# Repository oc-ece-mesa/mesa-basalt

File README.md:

# MESA Basalt

<div>

</div>

Basalt is a cost effective and easy to assemble (mostly through-hole components) devboard based on the STM32C071 microcontroller.

## Docs

1. [Parts List](docs/parts-list.md)
2. [Assembly & Setup](docs/assembly-and-setup.md)
3. [Dev Env Setup](docs/dev-env-setup.md)

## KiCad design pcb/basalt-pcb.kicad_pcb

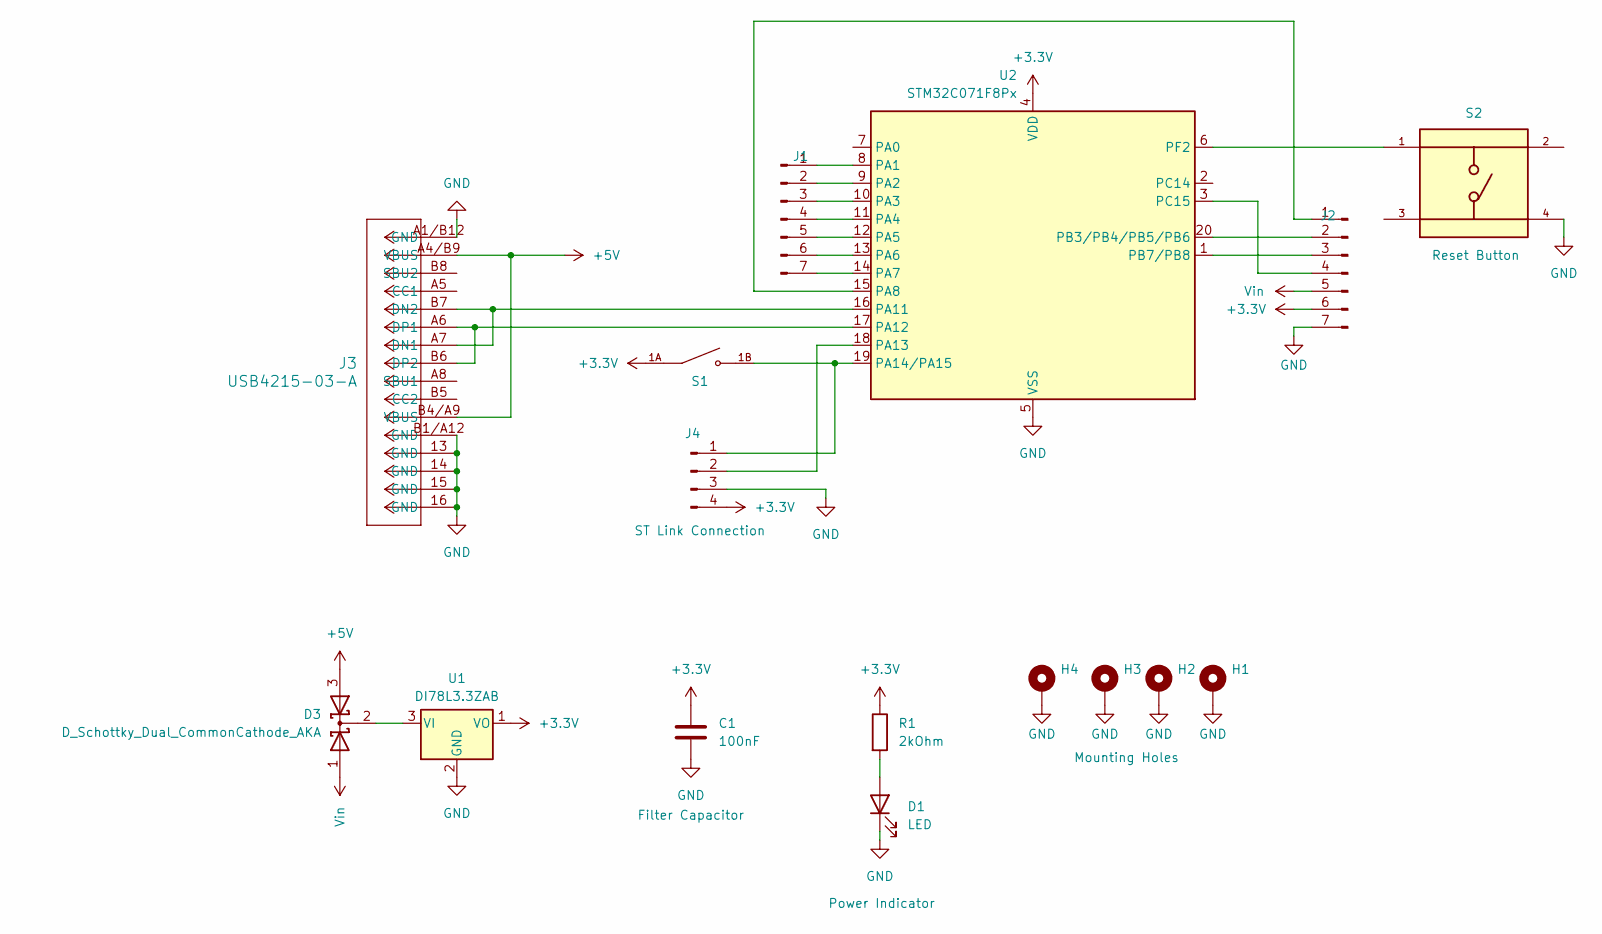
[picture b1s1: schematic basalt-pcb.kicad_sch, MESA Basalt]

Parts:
C1: 100nF; C_Disc_D5.1mm_W3.2mm_P5.00mm
D1: LED; LED_D3.0mm
D3: D_Schottky_Dual_CommonCathode_AKA; TO-220-3_Vertical
H1, H2, H3, H4: MountingHole_Pad; MountingHole_2.2mm_M2_Pad
J1, J2: Conn_01x07_Pin; PinHeader_1x07_P2.54mm_Vertical
J3: USB4215-03-A; CONN_8p94X6p5X3p16_12L_GCC
J4: Conn_01x04_Pin; PinHeader_1x04_P2.54mm_Vertical
R1: 2kOhm; R_Axial_DIN0309_L9.0mm_D3.2mm_P12.70mm_Horizontal
S1: DS04-254-1L-01BK; SW_DS04-254-1L-01BK; PARTREV V0.0
S2: TS02-66-50-BK-260-SCR-D; SW_TS02-66-50-BK-260-SCR-D; PARTREV 1.0
U1: DI78L3.3ZAB; TO-92_Inline
U2: STM32C071F8Px; TSSOP-20_4.4x6.5mm_P0.65mm

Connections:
+3.3V: C1.1, J2.6, J4.4, R1.1, S1.1A, U1.1 (VO), U2.4 (VDD)
+5V: D3.3 (A), J3.A4/B9 (VBUS), J3.B4/A9 (VBUS)
GND: C1.2, D1.1 (K), H1.1 (1_1), H2.1 (1_1), H3.1 (1_1), H4.1 (1_1), J2.7, J3.13 (GND), J3.14 (GND), J3.15 (GND), J3.16 (GND), J3.A1/B12 (GND), J3.B1/A12 (GND), J4.3, S2.4, U1.2 (GND), U2.5 (VSS)
unnamed: D1.2 (A), R1.2
unnamed: D3.2 (K), U1.3 (VI)
unnamed: J1.1, U2.8 (PA1)
unnamed: J1.2, U2.9 (PA2)
unnamed: J1.3, U2.10 (PA3)
unnamed: J1.4, U2.11 (PA4)
unnamed: J1.5, U2.12 (PA5)
unnamed: J1.6, U2.13 (PA6)
unnamed: J1.7, U2.14 (PA7)
unnamed: J2.1, U2.15 (PA8)
unnamed: J2.2, U2.20 (PB3/PB4/PB5/PB6)
unnamed: J2.3, U2.1 (PB7/PB8)
unnamed: J2.4, U2.3 (PC15)
unnamed: J3.A7 (DN1), J3.B7 (DN2), U2.16 (PA11)
unnamed: J3.A6 (DP1), J3.B6 (DP2), U2.17 (PA12)
unnamed: J4.1, S1.1B, U2.19 (PA14/PA15)
unnamed: J4.2, U2.18 (PA13)
unnamed: S2.1, U2.6 (PF2)
Vin: D3.1 (A), J2.5

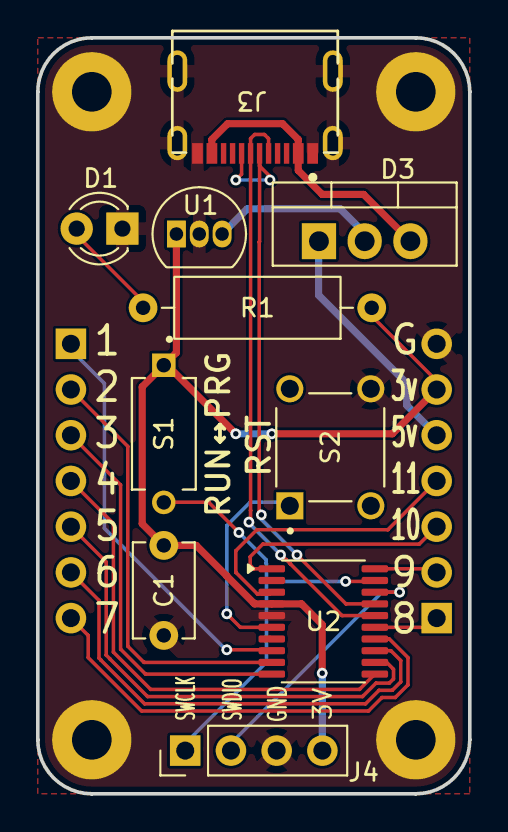
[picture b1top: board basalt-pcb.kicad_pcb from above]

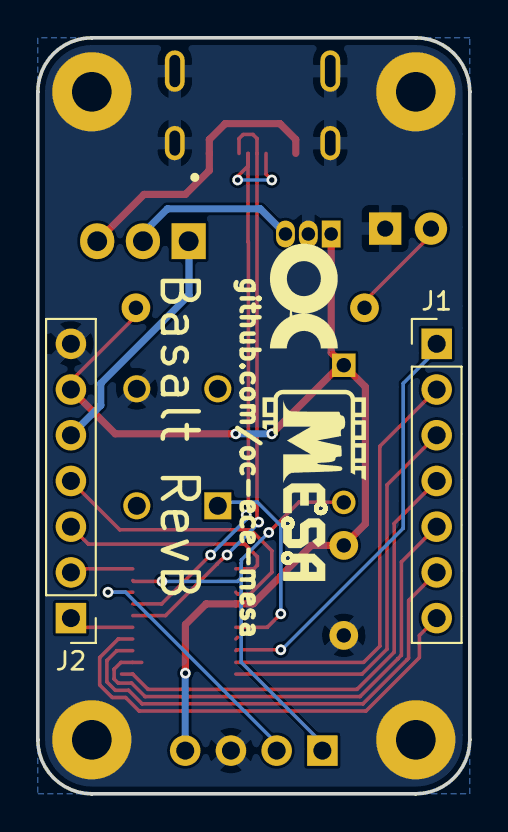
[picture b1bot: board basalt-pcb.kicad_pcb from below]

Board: 2 copper layers, 24.0 x 42.0 mm, 16 parts (2 on the bottom side), 22 nets.

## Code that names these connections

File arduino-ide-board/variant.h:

#pragma once

#define PA1     PIN_A1
#define PA2     PIN_A2
#define PA3     PIN_A3
#define PA4     PIN_A4
#define PA5     PIN_A5
#define PA6     PIN_A6
#define PA7     PIN_A7
#define PA8     PIN_A8
#define PB6     19
#define PB7     20
#define PC15    24

#define PINS_COUNT        11
#define NUM_DIGITAL_PINS  11
#define NUM_ANALOG_INPUTS 8

#define PIN_SERIAL_RX   PA3
#define PIN_SERIAL_TX   PA2

#define PIN_SPI_SS      PA4
#define PIN_SPI_MOSI    PA7
#define PIN_SPI_MISO    PA6
#define PIN_SPI_SCK     PA5

#define PIN_WIRE_SDA    PB7
#define PIN_WIRE_SCL    PB6

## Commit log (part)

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2026-04-20 Add .gitignore
2026-04-23 Add pcb and footprint
2026-04-23 Change folder name
2026-04-23 Update sym
2026-04-24 Expose more pins, add ST-link pins at back, add diode to prevent backfeeding USB port
2026-04-24 Label additions and tweaks to pcb. Update sym/footprint.
2026-04-25 Update gitignore
2026-04-30 Update with new pin count (removing pins that cannot be accessed with existing arduino ide variant), start work on arduino board config
2026-04-30 Add 3D models and 3D model images to README
2026-05-02 Switch to using STM32C071G8U6 that is supported by STM32duino currently
2026-05-02 Undo accidental merge...
2026-05-02 Increase power trace widths
2026-05-02 Small tweaks to PCB, add logo, etc.
2026-05-02 Small pcb tweaks
2026-05-02 minor changes to silkscreen
2026-05-02 Minor updates to pcb, update gitignore
2026-05-02 Minor edits to pcb and titleblocks
2026-05-02 Small updates
2026-05-03 Fix mounting holes
2026-05-04 Update kicad part footprint
2026-05-04 Update 3d images
2026-05-04 Add STEP file to kicad part folder
2026-05-15 Update, rev2, fix silkscreen and make board narrower
2026-05-15 Fix titleblocks (should be rev A)
2026-05-31 Update kicad parts, add model for socket headers
2026-05-31 Remove WIP arduino board variant folder
2026-05-31 Update images
2026-06-01 Add docs
2026-06-07 Add assembly and setup doc
2026-06-07 Update assembly doc
2026-06-14 Fix dev env setup image order
